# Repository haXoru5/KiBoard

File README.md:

# KiBoard
Custom mechanical keyboard built entirely from scratch

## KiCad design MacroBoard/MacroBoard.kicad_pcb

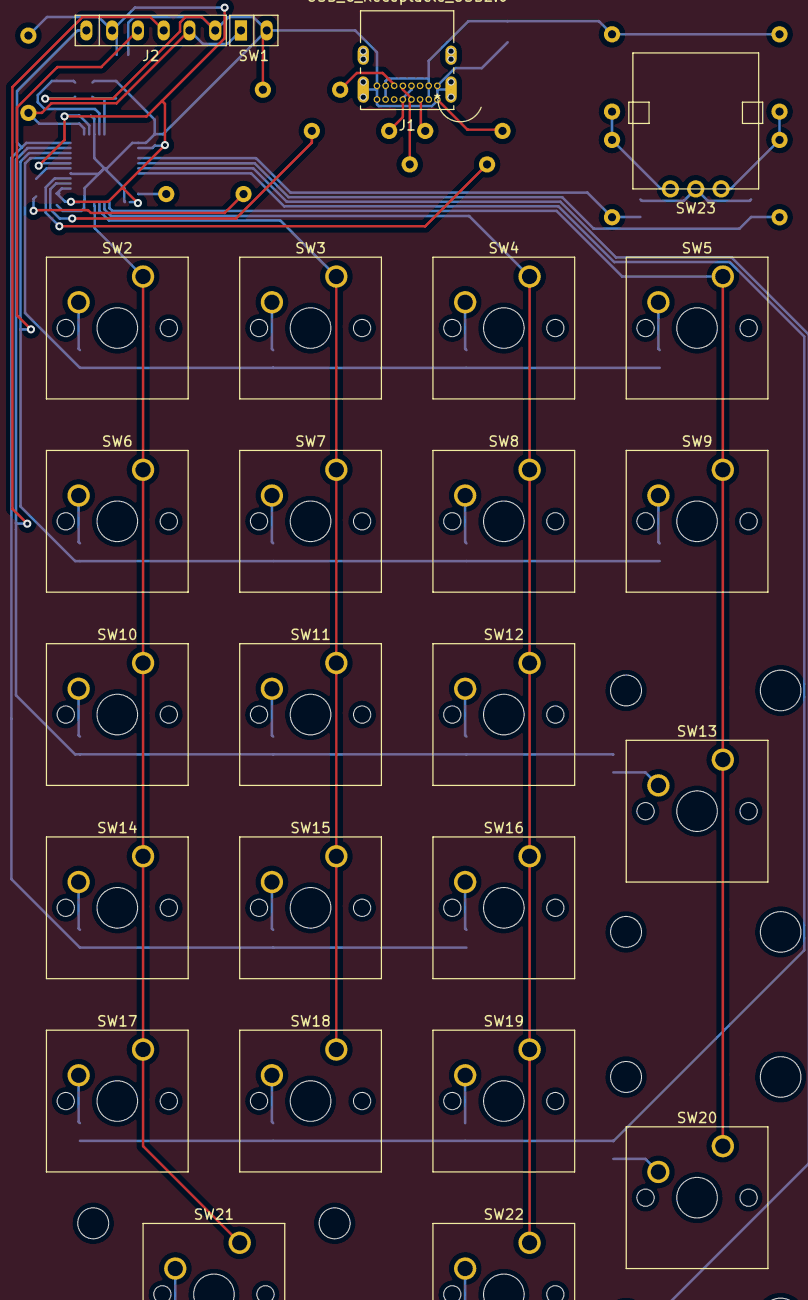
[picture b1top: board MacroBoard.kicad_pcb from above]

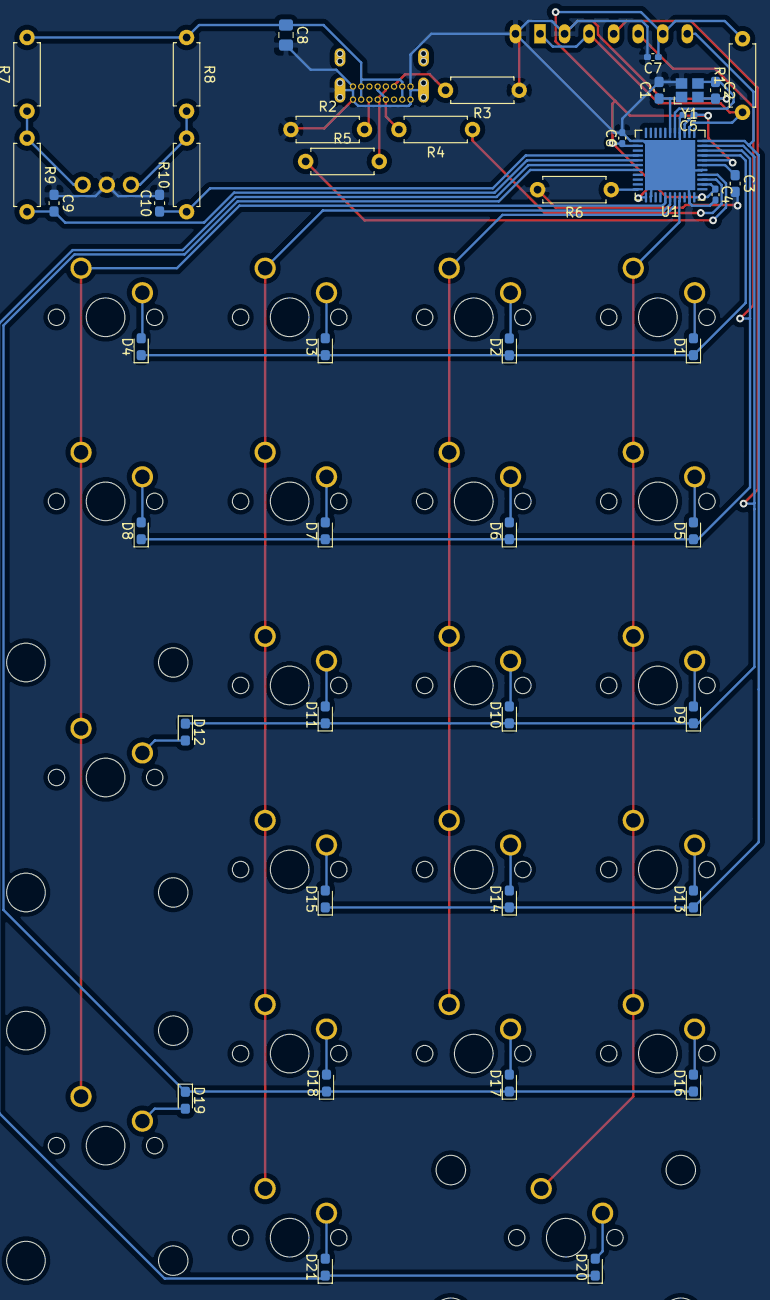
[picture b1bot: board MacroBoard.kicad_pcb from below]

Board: 2 copper layers, 68 parts (43 on the bottom side), 48 nets.

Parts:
C1, C2: 10pF; C_0603_1608Metric_Pad1.08x0.95mm_HandSolder
C3: 1uF; C_0603_1608Metric_Pad1.08x0.95mm_HandSolder
C4, C5, C6, C7: 100nF; C_0402_1005Metric_Pad0.74x0.62mm_HandSolder
C8: 10uF; C_0805_2012Metric_Pad1.18x1.45mm_HandSolder
C9, C10: 10nF; C_0603_1608Metric_Pad1.08x0.95mm_HandSolder
D1, D2, D3, D4, D5, D6, D7, D8, D9, D10, D11, D12, D13, D14, D15, D16, D17, D18, D19, D20, D21: D; D_0603_1608Metric_Pad1.05x0.95mm_HandSolder
J1: USB_C_Receptacle_USB2.0; USB4085-GF-A
J2: AVR-ISP-6; ISP
R1, R6, R7, R8, R9, R10: 10k; R_Axial_DIN0207_L6.3mm_D2.5mm_P7.62mm_Horizontal
R2, R3: 5k1; R_Axial_DIN0207_L6.3mm_D2.5mm_P7.62mm_Horizontal
R4, R5: 22; R_Axial_DIN0207_L6.3mm_D2.5mm_P7.62mm_Horizontal
SW1: SW_MEC_5G; Button_Breakout
SW2, SW3, SW4, SW5, SW6, SW7, SW8, SW9, SW10, SW11, SW12, SW14, SW15, SW16, SW17, SW18, SW19, SW22: SW_MEC_5G; SW_Cherry_MX_1.00u_PCB
SW13, SW20: SW_MEC_5G; SW_Cherry_MX_2.00u_Vertical_PCB
SW21: SW_MEC_5G; SW_Cherry_MX_2.00u_PCB
SW23: Rotary_Encoder
U1: ATmega32U4-MU; QFN-44-1EP_7x7mm_P0.5mm_EP5.2x5.2mm
Y1: Crystal_GND24_16MHz; FA-20H_Crystal

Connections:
Col0: SW2.1, SW6.1, SW10.1, SW14.1, SW17.1, SW21.1, U1.41
Col1: SW3.1, SW7.1, SW11.1, SW15.1, SW18.1, U1.40
Col2: SW4.1, SW8.1, SW12.1, SW16.1, SW19.1, SW22.1, U1.39
Col3: SW5.1, SW9.1, SW13.1, SW20.1, U1.38
GND: C1.2, C2.2, C3.2, C4.2, C5.2, C6.2, C7.2, C8.2, C9.1, C10.2, J1.A1, J1.A12, J1.B1, J1.B12, J1.S1, J2.6, R2.1, R3.1, R6.2, SW1.2, SW23.C, U1.5, U1.15, U1.23, U1.35, U1.43, U1.45, Y1.2, Y1.4
MISO: D13.1, D14.1, D15.1, J2.1, U1.11
MOSI: D9.1, D10.1, D11.1, D12.1, J2.4, U1.10
unnamed: C3.1, U1.6
unnamed: D1.2, SW2.2
unnamed: D2.2, SW3.2
unnamed: D3.2, SW4.2
unnamed: D4.2, SW5.2
unnamed: D5.2, SW6.2
unnamed: D6.2, SW7.2
unnamed: D7.2, SW8.2
unnamed: D8.2, SW9.2
unnamed: D9.2, SW10.2
unnamed: D10.2, SW11.2
unnamed: D11.2, SW12.2
unnamed: D12.2, SW13.2
unnamed: D13.2, SW14.2
unnamed: D14.2, SW15.2
unnamed: D15.2, SW16.2
unnamed: D16.2, SW17.2
unnamed: D17.2, SW18.2
unnamed: D18.2, SW19.2
unnamed: D19.2, SW20.2
unnamed: D20.2, SW21.2
unnamed: D21.2, SW22.2
unnamed: J1.A5, R2.2
unnamed: J1.A6, J1.B6, R5.2
unnamed: J1.A7, J1.B7, R4.2
unnamed: J1.B5, R3.2
unnamed: R4.1, U1.3
unnamed: R5.1, U1.4
unnamed: R6.1, U1.33
unnamed: R7.1, R9.1, SW23.B
unnamed: R8.2, R10.2, SW23.A
REA: C10.1, R10.1, U1.26
REB: C9.2, R9.2, U1.27
RST: J2.5, R1.1, SW1.1, U1.13
Row0: D1.1, D2.1, D3.1, D4.1, U1.8
Row1: D5.1, D6.1, D7.1, D8.1, J2.3, U1.9
Row4: D16.1, D17.1, D18.1, D19.1, U1.29
Row5: D20.1, D21.1, U1.28
VCC: C4.1, C5.1, C6.1, C7.1, C8.1, J1.A4, J1.A9, J1.B4, J1.B9, J2.2, R1.2, R7.2, R8.1, U1.2, U1.7, U1.14, U1.24, U1.34, U1.44
XTAL1: C1.1, U1.17, Y1.1
XTAL2: C2.1, U1.16, Y1.3

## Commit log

2022-01-15 added numpad
2022-02-01 finished schematic
2022-02-01 updated libraries
2022-02-05 Created pcb file
    To do:
    -borders
    -numlock LED
2022-02-16 remove redundant folders
